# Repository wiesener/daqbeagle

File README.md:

# daqbeagle
The daqbeagle is a data aquisition device for analog and digital signals and aswell combined 
with real-time capable target for simulink/matlab external mode. 
Together with a small shield it consists of three parts:

## 1. ERT linux target for beaglebone black
The targte is based on the lintarget from http://lintarget.sourceforge.net/. The main modifications are:
- bugfixes for multipla sample rates
- changed policy for C++ usage
- CTRL+C signal listener for safe abort of application
- Compile flags for non-external mode simulation

## 2. DAQ library for beaglebone black
The library consists of 5 blocks for data aquisition of

- 7 ADC channels at 12 bit
- 8 digital outputs
- 8 digital inputs
- 2 PWM outputs
- 2 DAC outputs (only working with shield or lowpass filter)

All blocks are build using the legacy code tool. So first the daqbeagle.m script has to be executed.
Inside the blocks one memory map for all blocks is used. So the device tree overlay is only used for 
configuration. This makes it possible to run the blocks up to 1 kHz with only slight overruns. 

## 3. DAQ shield for beaglebone black.
The shield is a small (8x8 cm) pcb which includes level-shifters for the ADC (-5V-5V, -10-10V), 
logic level shifters (3.3V -> 5V) and the output lowpass filter for the DAC. Furthermore it is needed to have 
an tranceiver for all sysconfig pins at the P8 header of the BBB to use them after boot.
Inside the beaglebone folder there are all config and dtbo files included which are needed to run the shield.
 
The software is released under GPL.

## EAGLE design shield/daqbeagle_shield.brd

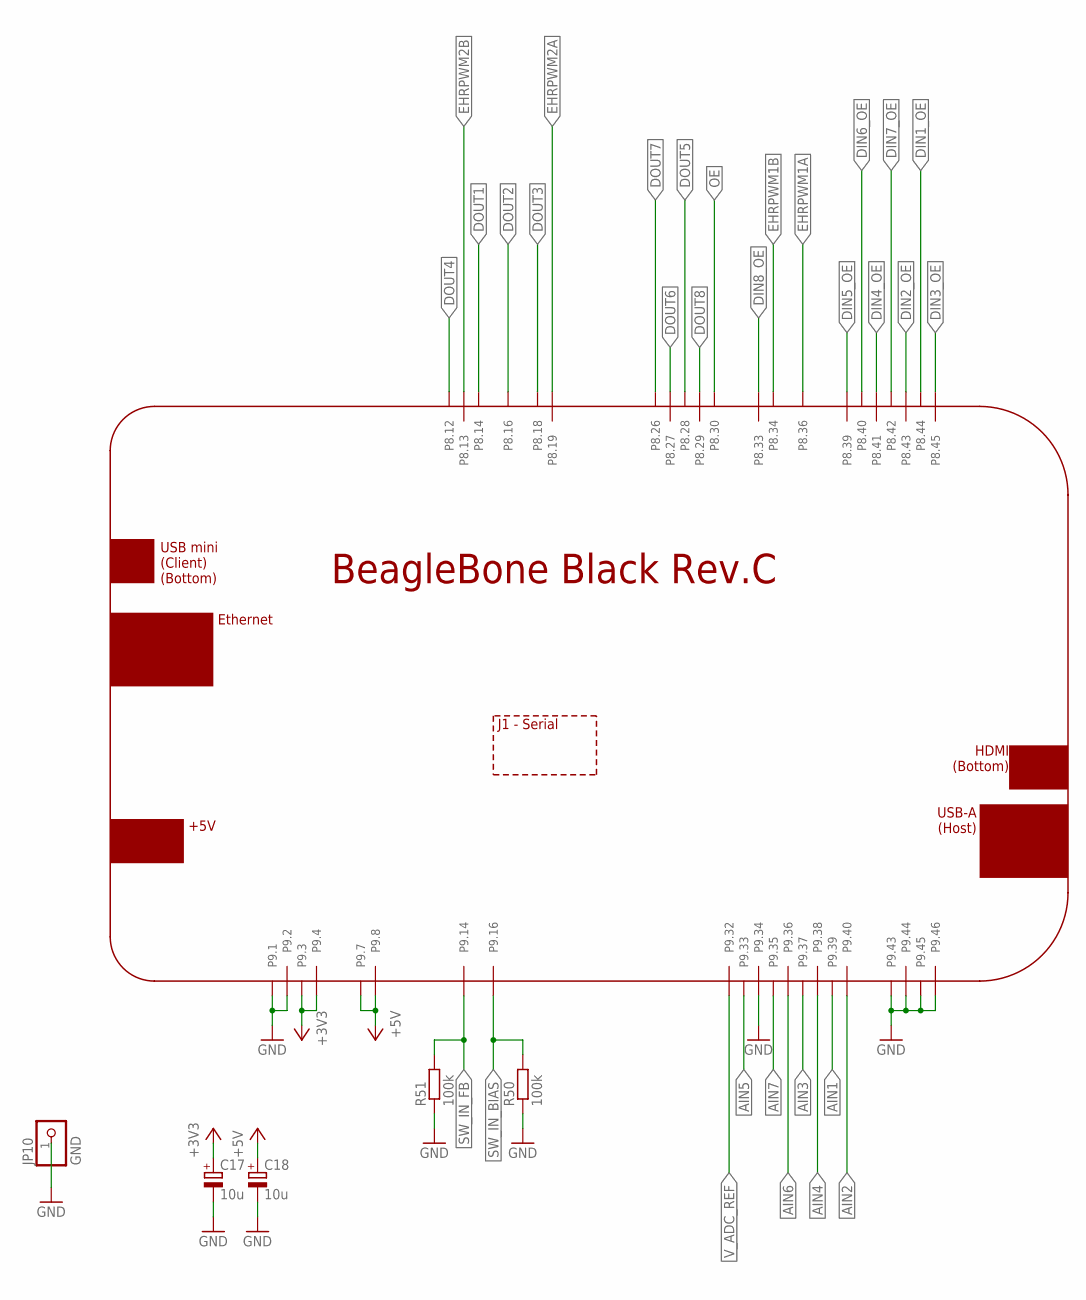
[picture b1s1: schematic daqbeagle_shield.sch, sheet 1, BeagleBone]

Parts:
C17: 10u; CT3216
C18: 10u; CT6032
JP10: GND; PAD
PCB1: BEAGLEBONE_BLACK
R50, R51: 100k; R0805

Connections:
+3V3: C17.+, PCB1.P9.3, PCB1.P9.4; also elsewhere on the board
+5V: C18.+, PCB1.P9.7, PCB1.P9.8; also elsewhere on the board
AIN1: PCB1.P9.39; also elsewhere on the board
AIN2: PCB1.P9.40; also elsewhere on the board
AIN3: PCB1.P9.37; also elsewhere on the board
AIN4: PCB1.P9.38; also elsewhere on the board
AIN5: PCB1.P9.33; also elsewhere on the board
AIN6: PCB1.P9.36; also elsewhere on the board
AIN7: PCB1.P9.35; also elsewhere on the board
DIN1_OE: PCB1.P8.44; also elsewhere on the board
DIN2_OE: PCB1.P8.43; also elsewhere on the board
DIN3_OE: PCB1.P8.45; also elsewhere on the board
DIN4_OE: PCB1.P8.41; also elsewhere on the board
DIN5_OE: PCB1.P8.39; also elsewhere on the board
DIN6_OE: PCB1.P8.40; also elsewhere on the board
DIN7_OE: PCB1.P8.42; also elsewhere on the board
DIN8_OE: PCB1.P8.33; also elsewhere on the board
DOUT1: PCB1.P8.14; also elsewhere on the board
DOUT2: PCB1.P8.16; also elsewhere on the board
DOUT3: PCB1.P8.18; also elsewhere on the board
DOUT4: PCB1.P8.12; also elsewhere on the board
DOUT5: PCB1.P8.28; also elsewhere on the board
DOUT6: PCB1.P8.27; also elsewhere on the board
DOUT7: PCB1.P8.26; also elsewhere on the board
DOUT8: PCB1.P8.29; also elsewhere on the board
EHRPWM1A: PCB1.P8.36; also elsewhere on the board
EHRPWM1B: PCB1.P8.34; also elsewhere on the board
EHRPWM2A: PCB1.P8.19; also elsewhere on the board
EHRPWM2B: PCB1.P8.13; also elsewhere on the board
GND: C17.-, C18.-, JP10.1, PCB1.P9.1, PCB1.P9.2, PCB1.P9.34, PCB1.P9.43, PCB1.P9.44, PCB1.P9.45, PCB1.P9.46, R50.1, R51.1; also elsewhere on the board
OE: PCB1.P8.30; also elsewhere on the board
SW_IN_BIAS: PCB1.P9.16, R50.2; also elsewhere on the board
SW_IN_FB: PCB1.P9.14, R51.2; also elsewhere on the board
V_ADC_REF: PCB1.P9.32; also elsewhere on the board

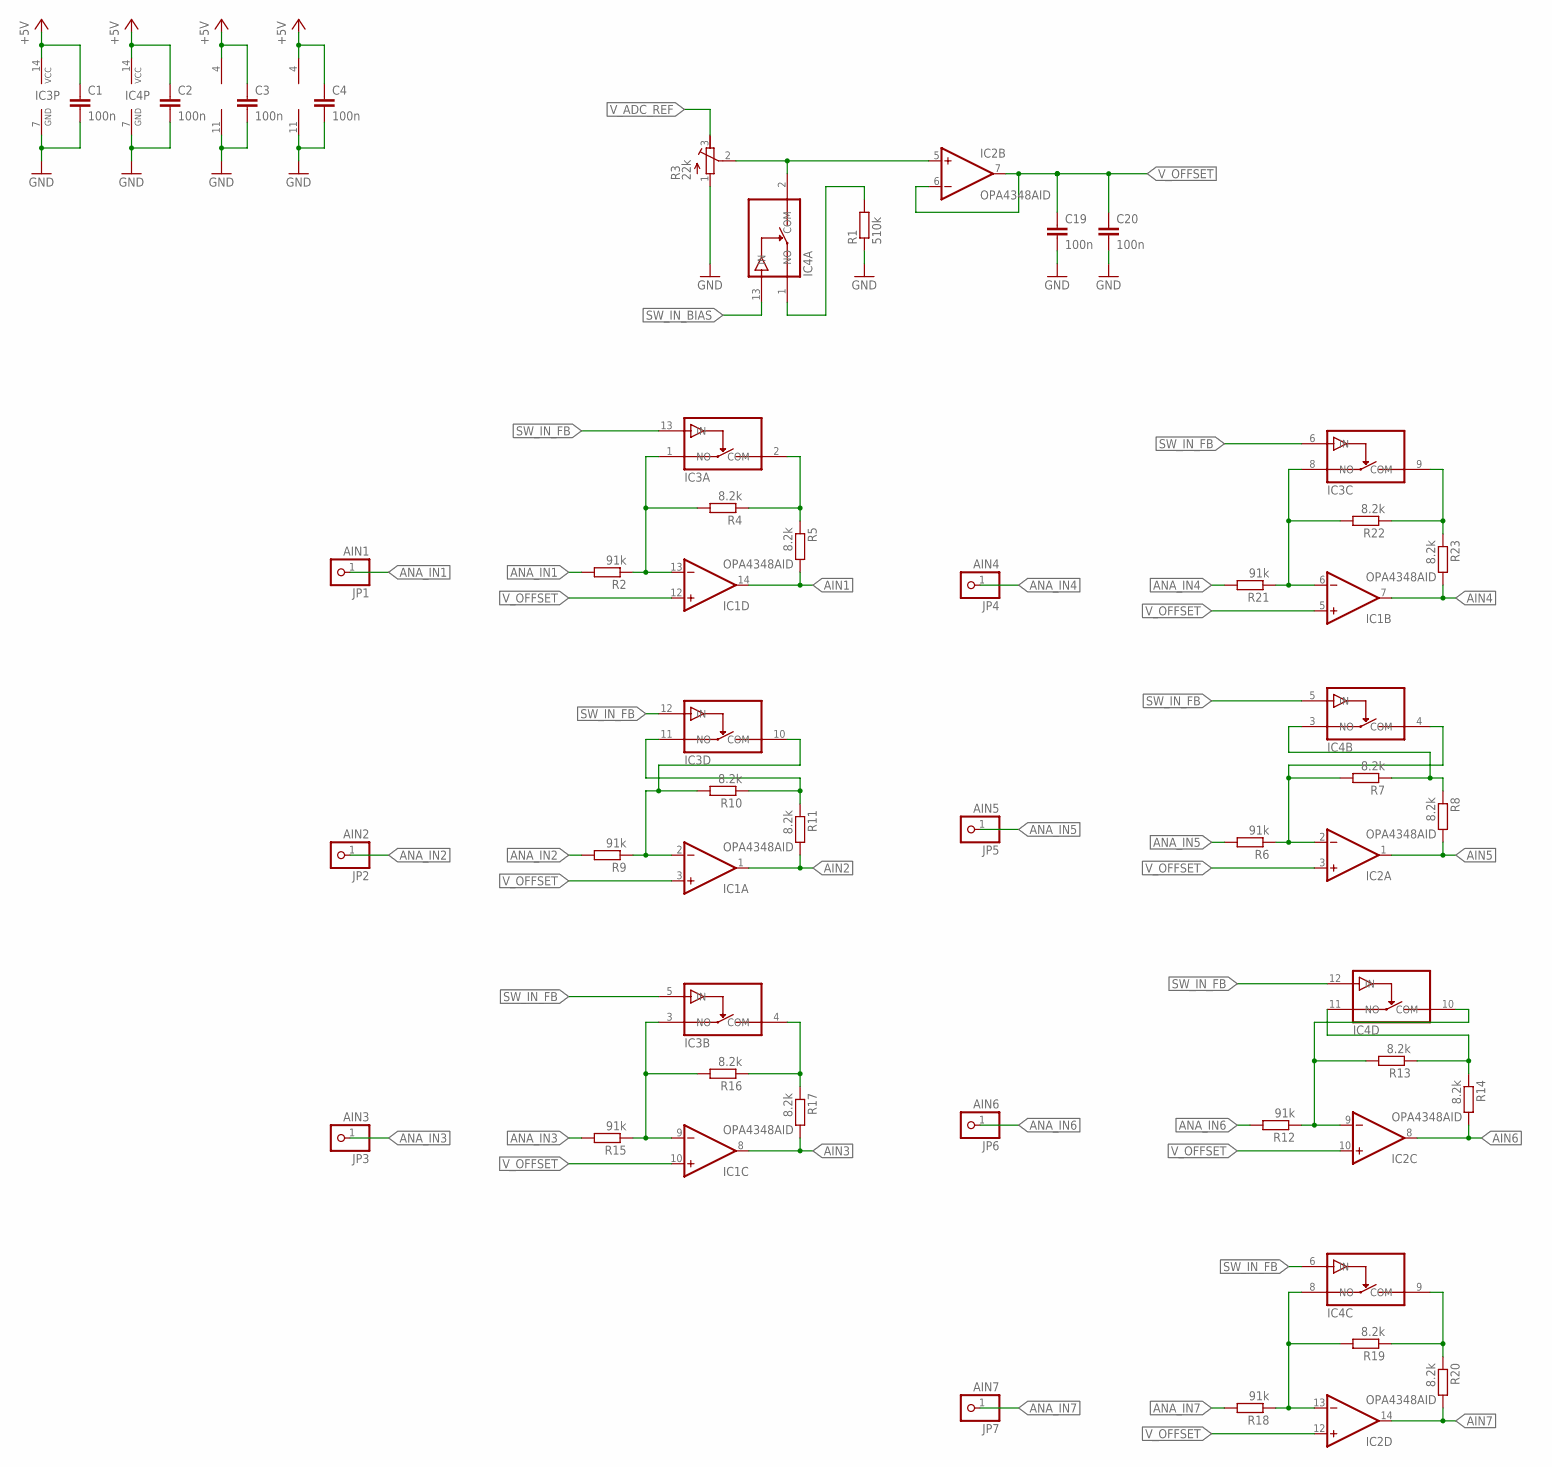
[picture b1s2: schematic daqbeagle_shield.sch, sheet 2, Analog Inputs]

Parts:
C1, C2, C3, C4, C19, C20: 100n; C0805
IC1, IC2: OPA4348AID; SO14
IC3, IC4: TS12A44514PW; TSSOP14
JP1: AIN1; PAD
JP2: AIN2; PAD
JP3: AIN3; PAD
JP4: AIN4; PAD
JP5: AIN5; PAD
JP6: AIN6; PAD
JP7: AIN7; PAD
R1: 510k; R0603
R2, R6, R9, R12, R15, R18, R21: 91k; R0603
R3: 22k; RTRIM3296P
R4, R5, R7, R8, R10, R11, R13, R14, R16, R17, R19, R20, R22, R23: 8.2k; R0603

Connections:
+5V: C1.1, C2.1, C3.1, C4.1, IC1.4 (V+), IC2.4 (V+), IC3.14 (VCC), IC4.14 (VCC); also elsewhere on the board
AIN1: IC1.14 (OUT), R5.2; also elsewhere on the board
AIN2: IC1.1 (OUT), R11.2; also elsewhere on the board
AIN3: IC1.8 (OUT), R17.2; also elsewhere on the board
AIN4: IC1.7 (OUT), R23.2; also elsewhere on the board
AIN5: IC2.1 (OUT), R8.2; also elsewhere on the board
AIN6: IC2.8 (OUT), R14.2; also elsewhere on the board
AIN7: IC2.14 (OUT), R20.2; also elsewhere on the board
ANA_IN1: JP1.1, R2.2
ANA_IN2: JP2.1, R9.2
ANA_IN3: JP3.1, R15.2
ANA_IN4: JP4.1, R21.2
ANA_IN5: JP5.1, R6.2
ANA_IN6: JP6.1, R12.2
ANA_IN7: JP7.1, R18.2
GND: C1.2, C2.2, C3.2, C4.2, C19.2, C20.2, IC1.11 (GND), IC2.11 (GND), IC3.7 (GND), IC4.7 (GND), R1.1, R3.1 (A); also elsewhere on the board
unnamed: IC2.5 (+IN), IC4.2 (COM), R3.2 (S)
unnamed: IC4.1 (NO), R1.2
unnamed: IC1.13 (-IN), IC3.1 (NO), R2.1, R4.2
unnamed: IC2.2 (-IN), IC4.4 (COM), R6.1, R7.2
unnamed: IC4.3 (NO), R7.1, R8.1
unnamed: IC3.2 (COM), R4.1, R5.1
unnamed: IC1.2 (-IN), IC3.10 (COM), R9.1, R10.2
unnamed: IC3.11 (NO), R10.1, R11.1
unnamed: IC2.9 (-IN), IC4.10 (COM), R12.1, R13.2
unnamed: IC4.11 (NO), R13.1, R14.1
unnamed: IC3.4 (COM), R16.1, R17.1
unnamed: IC2.13 (-IN), IC4.8 (NO), R18.1, R19.2
unnamed: IC4.9 (COM), R19.1, R20.1
unnamed: IC1.6 (-IN), IC3.8 (NO), R21.1, R22.2
unnamed: IC3.9 (COM), R22.1, R23.1
unnamed: IC1.9 (-IN), IC3.3 (NO), R15.1, R16.2
SW_IN_BIAS: IC4.13 (IN); also elsewhere on the board
SW_IN_FB: IC3.5 (IN), IC3.6 (IN), IC3.12 (IN), IC3.13 (IN), IC4.5 (IN), IC4.6 (IN), IC4.12 (IN); also elsewhere on the board
V_ADC_REF: R3.3 (E); also elsewhere on the board
V_OFFSET: C19.1, C20.1, IC1.3 (+IN), IC1.5 (+IN), IC1.10 (+IN), IC1.12 (+IN), IC2.3 (+IN), IC2.6 (-IN), IC2.7 (OUT), IC2.10 (+IN), IC2.12 (+IN)

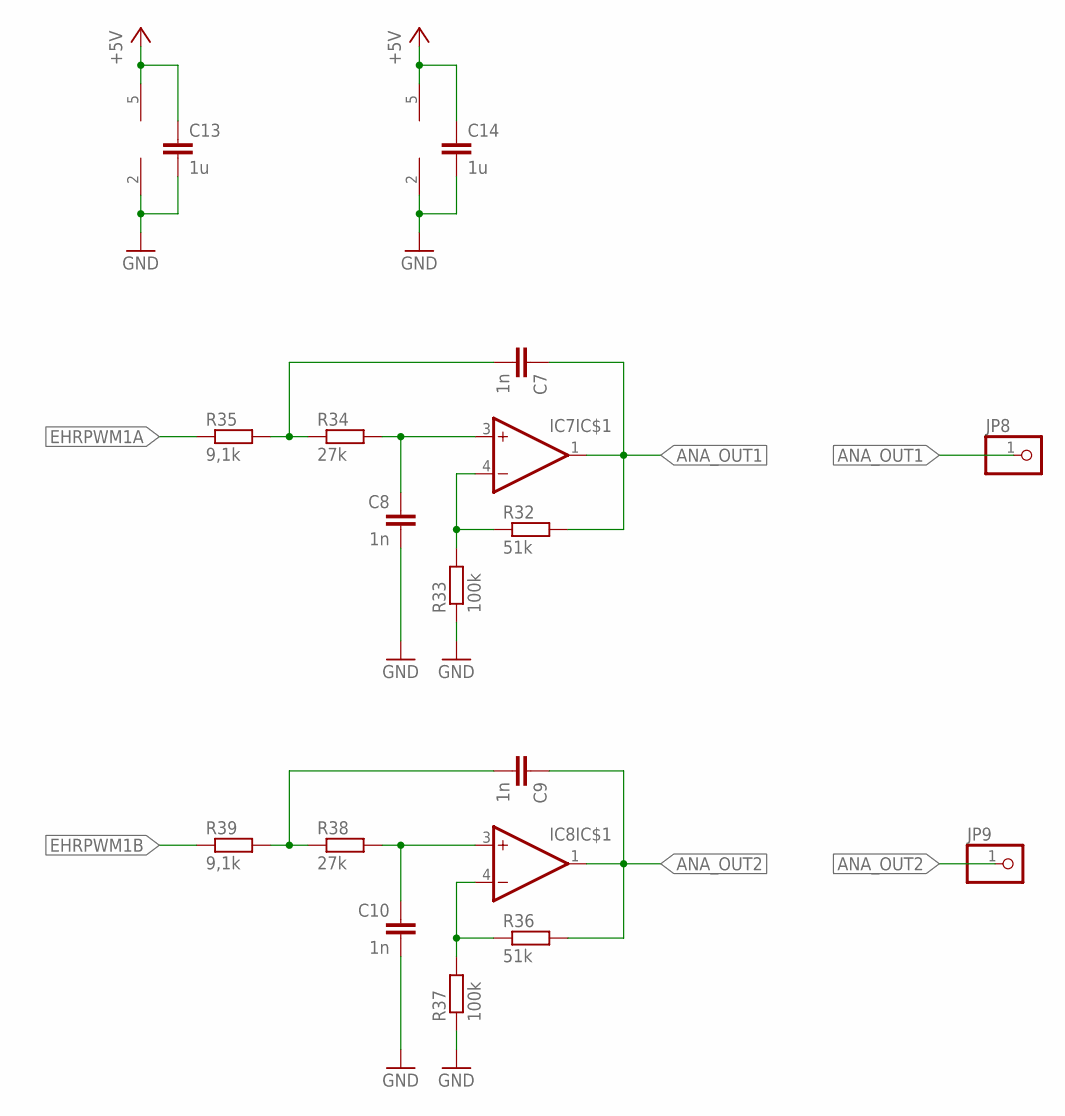
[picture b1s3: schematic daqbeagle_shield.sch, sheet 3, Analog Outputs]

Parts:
C7, C8, C9, C10: 1n; C0805
C13, C14: 1u; C0805
IC7, IC8: OPA320; SOT23-5L
JP8, JP9: SOLDER_PAD; PAD
R32, R36: 51k; R0805
R33, R37: 100k; R0603
R34, R38: 27k; R0603
R35, R39: 9,1k; R0805

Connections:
+5V: C13.1, C14.1, IC7.5 (V+), IC8.5 (V+); also elsewhere on the board
ANA_OUT1: C7.1, IC7.1 (OUT), JP8.1, R32.2
ANA_OUT2: C9.1, IC8.1 (OUT), JP9.1, R36.2
EHRPWM1A: R35.1; also elsewhere on the board
EHRPWM1B: R39.1; also elsewhere on the board
GND: C8.2, C10.2, C13.2, C14.2, IC7.2 (GND), IC8.2 (GND), R33.1, R37.1; also elsewhere on the board
unnamed: IC7.4 (-IN), R32.1, R33.2
unnamed: IC8.4 (-IN), R36.1, R37.2
unnamed: C8.1, IC7.3 (+IN), R34.2
unnamed: C7.2, R34.1, R35.2
unnamed: C10.1, IC8.3 (+IN), R38.2
unnamed: C9.2, R38.1, R39.2

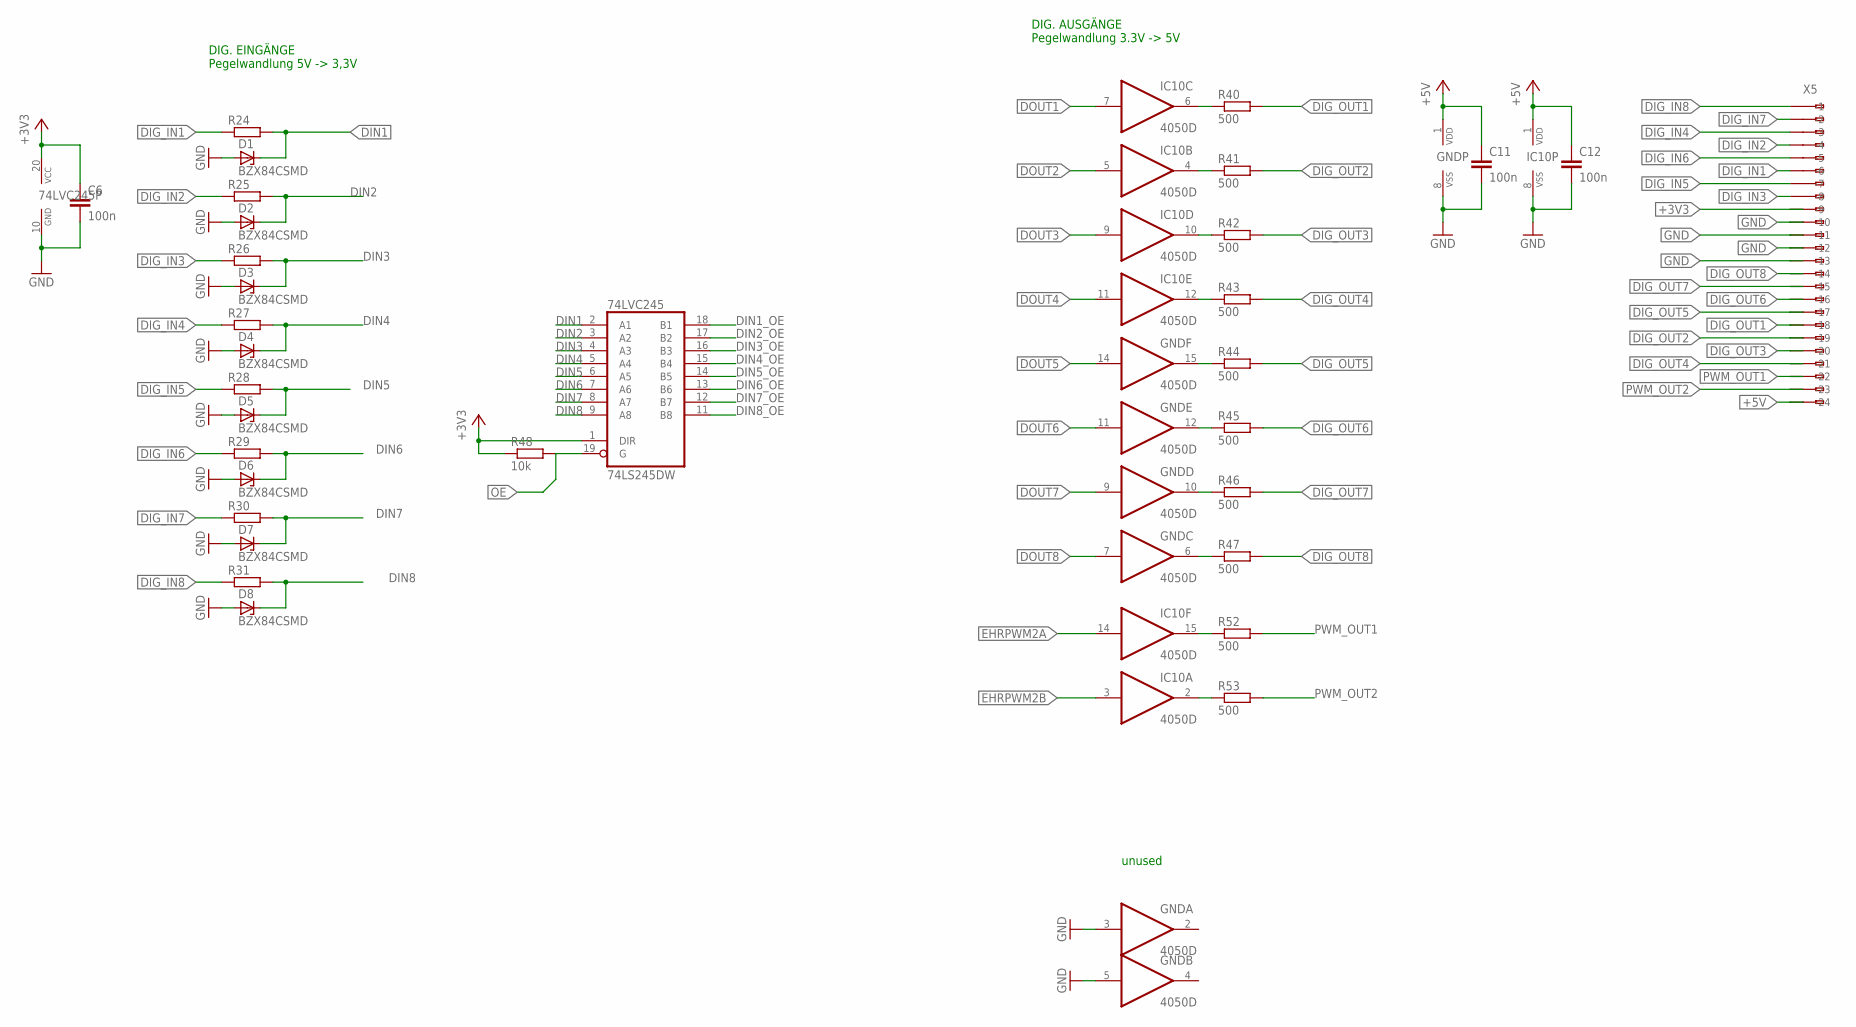
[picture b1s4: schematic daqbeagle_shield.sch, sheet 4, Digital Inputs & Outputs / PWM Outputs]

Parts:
74LVC245: 74LS245DW; SO20W
C6, C11, C12: 100n; C0805
D1, D2, D3, D4, D5, D6, D7, D8: BZX84CSMD; TO236
GND: 4050D; SO16
IC10: 4050D; SO16
R24, R25, R26, R27, R28, R29, R30, R31: R-EU_R0805; R0805
R40, R41, R42, R43, R44, R45, R46, R47, R52, R53: 500; R0805
R48: 10k; R0805
X5: 233-124

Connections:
+3V3: 74LVC245.1 (DIR), 74LVC245.20 (VCC), C6.1, R48.1, X5.A9 (-9), X5.B9 (B-9); also elsewhere on the board
+5V: C11.1, C12.1, GND.1 (VDD), IC10.1 (VDD), X5.A24 (-24), X5.B24 (B-24); also elsewhere on the board
DIG_IN1: R24.1, X5.A6 (-6)
DIG_IN2: R25.1, X5.A4 (-4)
DIG_IN3: R26.1, X5.A8 (-8)
DIG_IN4: R27.1, X5.A3 (-3)
DIG_IN5: R28.1, X5.A7 (-7)
DIG_IN6: R29.1, X5.A5 (-5)
DIG_IN7: R30.1, X5.A2 (-2)
DIG_IN8: R31.1, X5.A1 (-1)
DIG_OUT1: R40.2, X5.A18 (-18), X5.B18 (B-18)
DIG_OUT2: R41.2, X5.A19 (-19), X5.B19 (B-19)
DIG_OUT3: R42.2, X5.A20 (-20), X5.B20 (B-20)
DIG_OUT4: R43.2, X5.A21 (-21), X5.B21 (B-21)
DIG_OUT5: R44.2, X5.A17 (-17), X5.B17 (B-17)
DIG_OUT6: R45.2, X5.A16 (-16), X5.B16 (B-16)
DIG_OUT7: R46.2, X5.A15 (-15), X5.B15 (B-15)
DIG_OUT8: R47.2, X5.A14 (-14), X5.B14 (B-14)
DIN1: 74LVC245.2 (A1), D1.C, R24.2
DIN1_OE: 74LVC245.18 (B1); also elsewhere on the board
DIN2: 74LVC245.3 (A2), D2.C, R25.2
DIN2_OE: 74LVC245.17 (B2); also elsewhere on the board
DIN3: 74LVC245.4 (A3), D3.C, R26.2
DIN3_OE: 74LVC245.16 (B3); also elsewhere on the board
DIN4: 74LVC245.5 (A4), D4.C, R27.2
DIN4_OE: 74LVC245.15 (B4); also elsewhere on the board
DIN5: 74LVC245.6 (A5), D5.C, R28.2
DIN5_OE: 74LVC245.14 (B5); also elsewhere on the board
DIN6: 74LVC245.7 (A6), D6.C, R29.2
DIN6_OE: 74LVC245.13 (B6); also elsewhere on the board
DIN7: 74LVC245.8 (A7), D7.C, R30.2
DIN7_OE: 74LVC245.12 (B7); also elsewhere on the board
DIN8: 74LVC245.9 (A8), D8.C, R31.2
DIN8_OE: 74LVC245.11 (B8); also elsewhere on the board
DOUT1: IC10.7 (I); also elsewhere on the board
DOUT2: IC10.5 (I); also elsewhere on the board
DOUT3: IC10.9 (I); also elsewhere on the board
DOUT4: IC10.11 (I); also elsewhere on the board
DOUT5: GND.14 (I); also elsewhere on the board
DOUT6: GND.11 (I); also elsewhere on the board
DOUT7: GND.9 (I); also elsewhere on the board
DOUT8: GND.7 (I); also elsewhere on the board
EHRPWM2A: IC10.14 (I); also elsewhere on the board
EHRPWM2B: IC10.3 (I); also elsewhere on the board
GND: 74LVC245.10 (GND), C6.2, C11.2, C12.2, D1.A, D2.A, D3.A, D4.A, D5.A, D6.A, D7.A, D8.A, GND.3 (I), GND.5 (I), GND.8 (VSS), IC10.8 (VSS), X5.A10 (-10), X5.A11 (-11), X5.A12 (-12), X5.A13 (-13), X5.B10 (B-10), X5.B11 (B-11), X5.B12 (B-12), X5.B13 (B-13); also elsewhere on the board
unnamed: IC10.6 (O), R40.1
unnamed: IC10.4 (O), R41.1
unnamed: IC10.10 (O), R42.1
unnamed: IC10.12 (O), R43.1
unnamed: GND.15 (O), R44.1
unnamed: GND.12 (O), R45.1
unnamed: GND.10 (O), R46.1
unnamed: GND.6 (O), R47.1
unnamed: IC10.15 (O), R52.1
unnamed: IC10.2 (O), R53.1
OE: 74LVC245.19 (G), R48.2; also elsewhere on the board
PWM_OUT1: R52.2, X5.A22 (-22), X5.B22 (B-22)
PWM_OUT2: R53.2, X5.A23 (-23), X5.B23 (B-23)

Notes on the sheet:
DIG. EINGÄNGE Pegelwandlung 5V -> 3,3V
DIG. AUSGÄNGE Pegelwandlung 3.3V -> 5V
unused

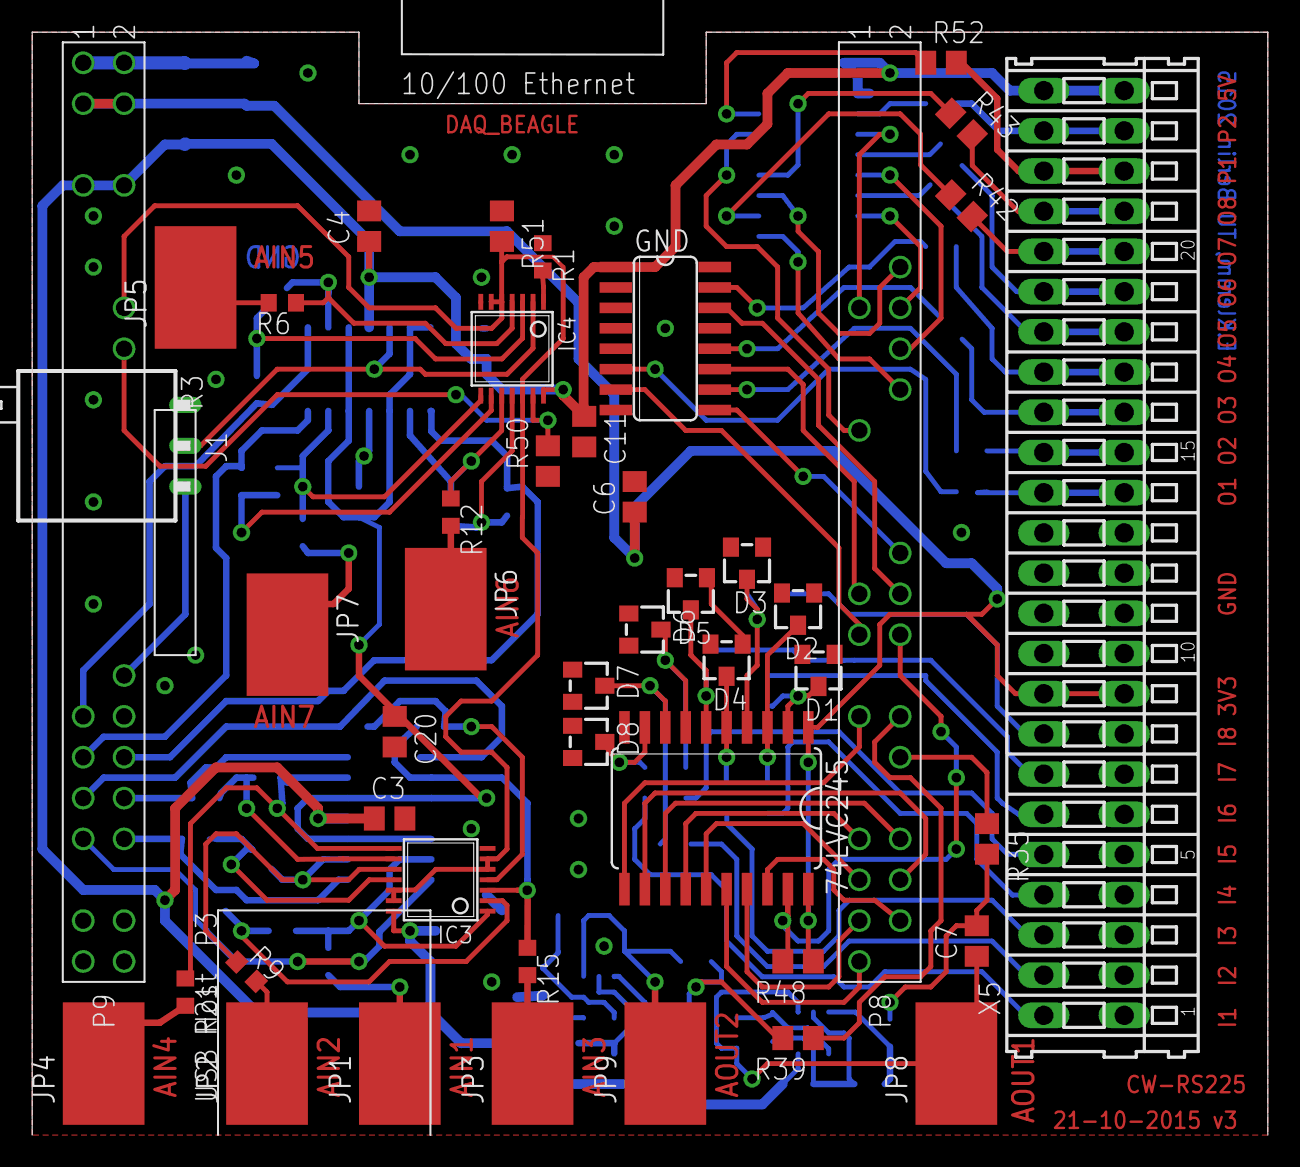
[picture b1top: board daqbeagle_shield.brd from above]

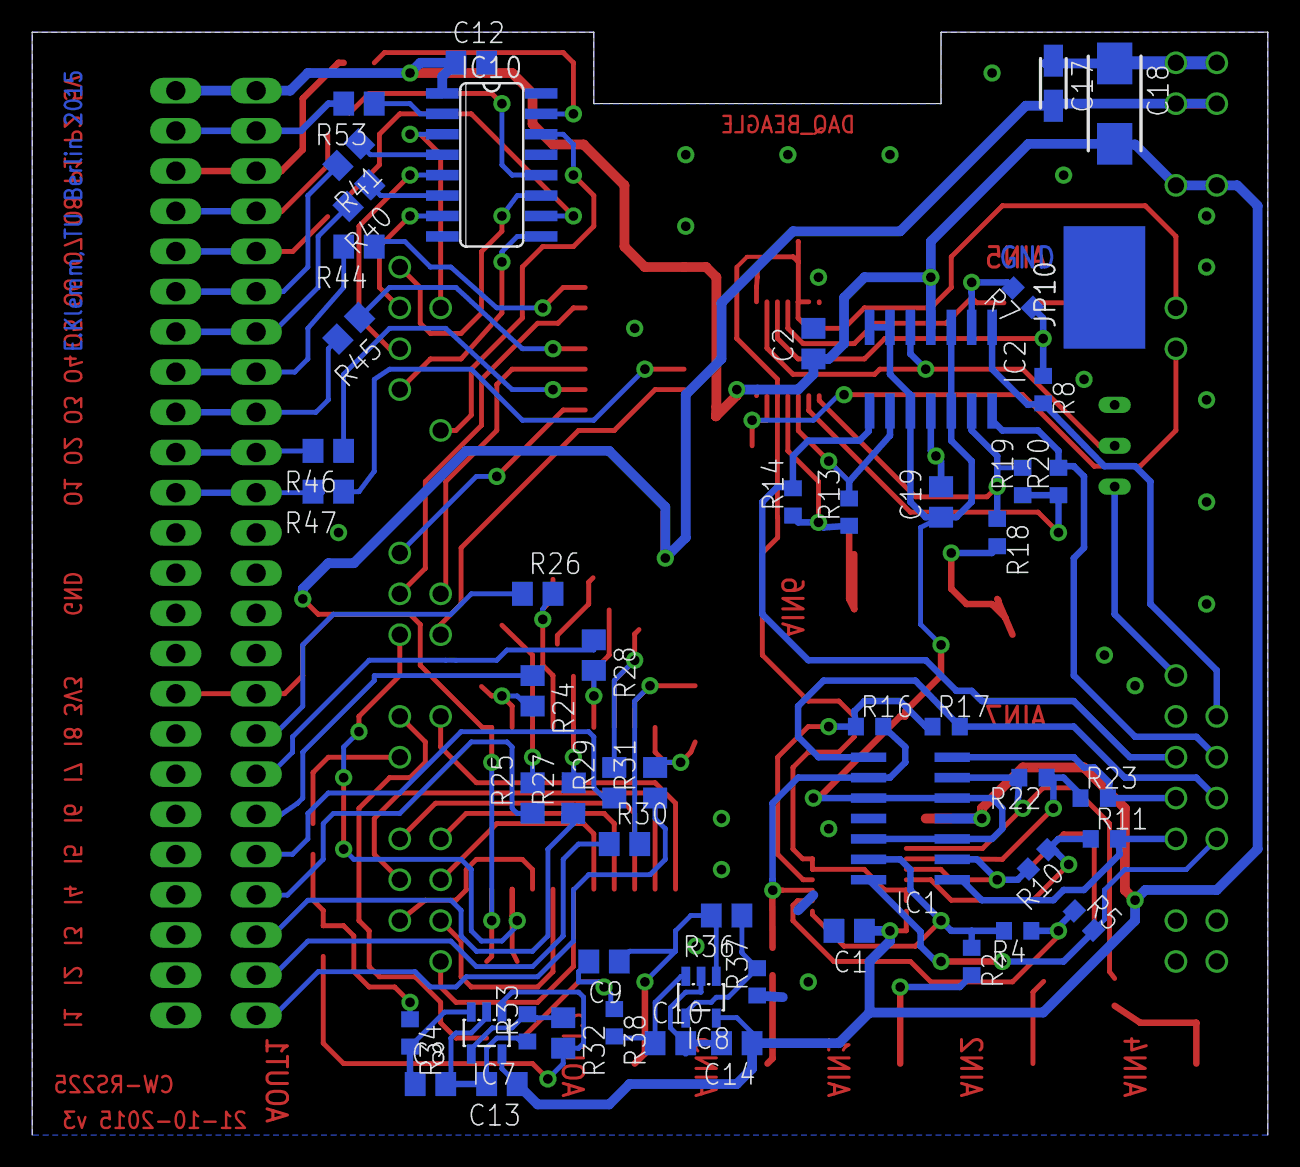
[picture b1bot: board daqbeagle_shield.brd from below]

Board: 2 copper layers, 76.8 x 68.6 mm, 98 parts (54 on the bottom side), 102 nets.

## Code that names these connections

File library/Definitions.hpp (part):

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enum adcName
{
  AIN0 = 0,
  AIN1 = 1,
  AIN2 = 2,
  AIN3 = 3,
  AIN4 = 4,
  AIN5 = 5,
  AIN6 = 6
};

typedef struct s_PIN {
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
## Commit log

2015-11-24 GPL licence added
2015-11-24 Changed to LICENCE
2015-11-24 Ready added
2015-11-24 no message
2015-11-24 folder added
2015-11-24 Eagle files added
2017-07-17 "Deleted runtarget"

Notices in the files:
library/Definitions.hpp:
Copyright (c) TU Berlin
